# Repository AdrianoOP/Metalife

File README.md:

Metalife
========

Projeto pessoal

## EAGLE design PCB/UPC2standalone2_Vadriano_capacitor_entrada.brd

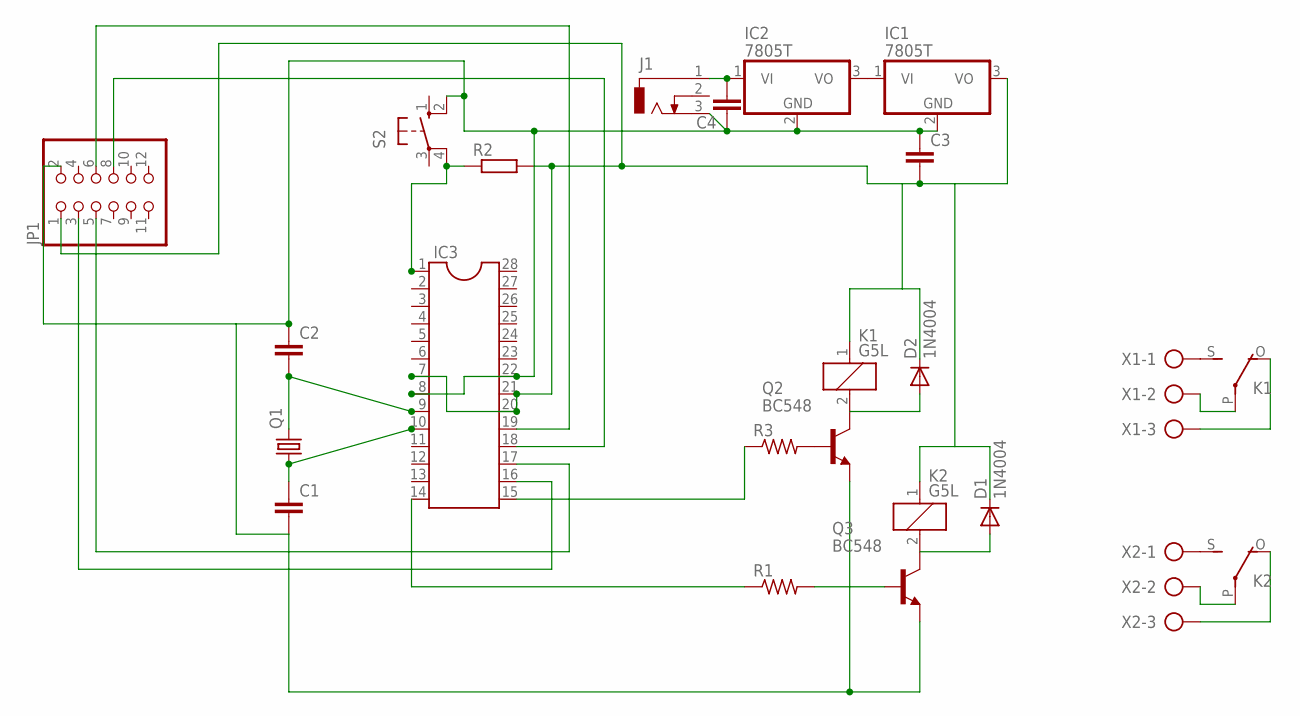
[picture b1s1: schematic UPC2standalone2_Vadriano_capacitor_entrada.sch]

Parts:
C1, C2, C3, C4: C5/5; C5B5
D1, D2: 1N4004; DO41-10
IC1, IC2: 7805T; TO220H
IC3: DIL28-3
J1: DCJ0303
JP1: PINHD-2X6; 2X06
K1, K2: G5L; G5LE
Q1: CRYSTALHC49U70; HC49U70
Q2, Q3: BC548; TO92-EBC
R1, R3: R-US_0207/10; 0207/10
R2: R-EU_0207/10; 0207/10
S2: 10-XX; B3F-10XX
X1, X2: AK300/3

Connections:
GND: C1.2, C2.1, C3.1, C4.1, IC1.2 (GND), IC2.2 (GND), IC3.8, IC3.22, J1.3, JP1.2, Q2.E, Q3.E, S2.2 (S1)
unnamed: IC3.18, JP1.8
unnamed: C1.1, IC3.10, Q1.1
unnamed: IC3.1, R2.1, S2.4 (P1)
unnamed: Q2.B, R3.2
unnamed: D2.A, K1.2, Q2.C
unnamed: IC3.16, JP1.3
unnamed: IC3.19, JP1.6
unnamed: IC3.17, JP1.5
unnamed: D1.A, K2.2, Q3.C
unnamed: Q3.B, R1.2
unnamed: IC3.15, R3.1
unnamed: IC1.1 (VI), IC2.3 (VO)
unnamed: C3.2, D1.C, D2.C, IC1.3 (VO), IC3.7, IC3.20, IC3.21, JP1.1, K1.1, K2.1, R2.2
unnamed: IC3.14, R1.1
unnamed: K1.S, X1.1
unnamed: K2.S, X2.1
unnamed: K2.P, X2.2
unnamed: K2.O, X2.3
unnamed: K1.P, X1.2
unnamed: K1.O, X1.3
unnamed: C4.2, IC2.1 (VI), J1.1
unnamed: C2.2, IC3.9, Q1.2

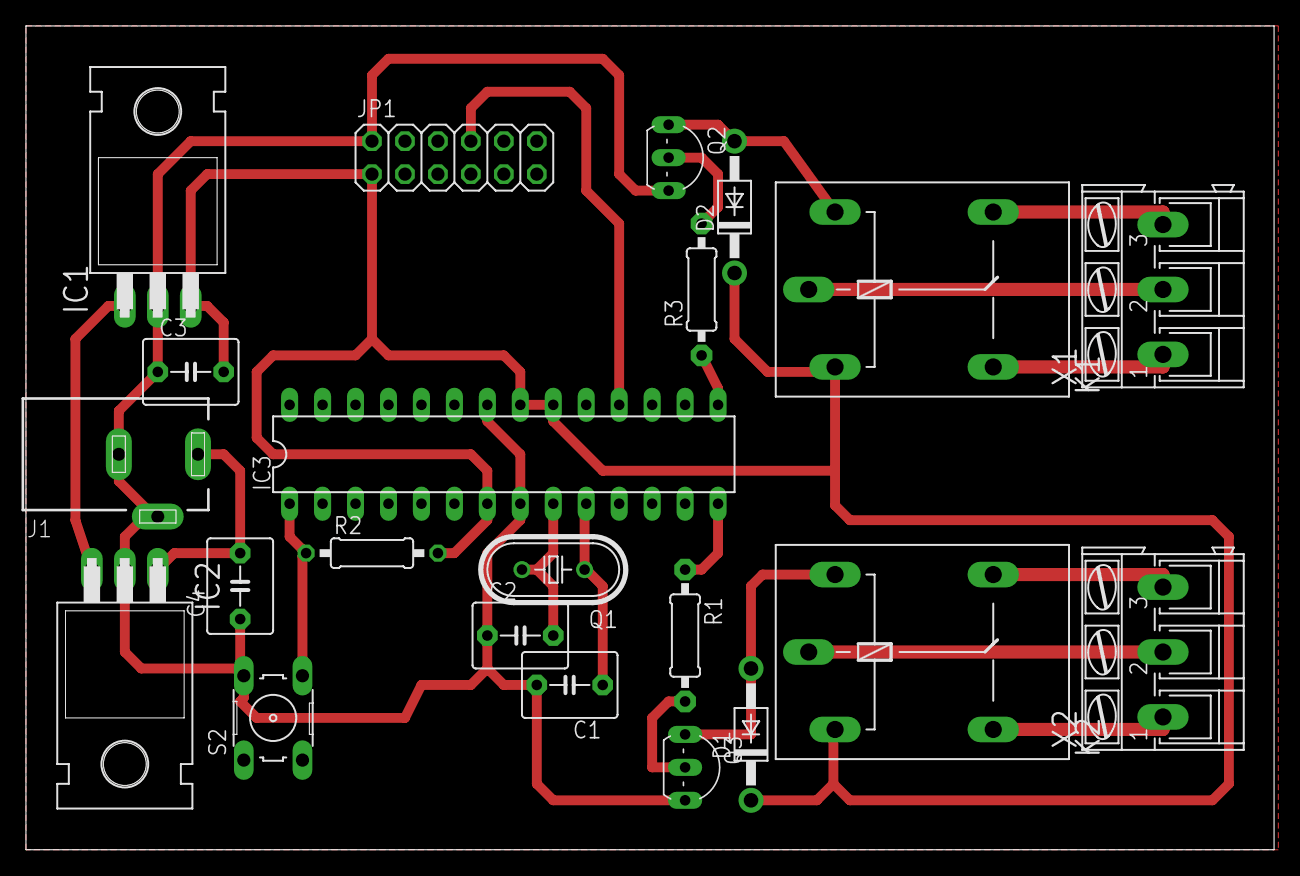
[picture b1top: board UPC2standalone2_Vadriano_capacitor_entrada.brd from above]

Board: 2 copper layers, 96.2 x 63.5 mm, 22 parts (0 on the bottom side), 23 nets.

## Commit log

2013-07-30 Primeira versão funcional do protótipo para a Metalife Apenas texto para o commit Esperamos que o repositorio seja bem utilizado
    Please enter the commit message for your changes. Lines starting
